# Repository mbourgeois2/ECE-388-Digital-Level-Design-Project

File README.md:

# ECE-388-Digital-Level-Design-Project
This is my Embedded Systems Design Project for ECE-388, the digital level. The design works as follows. The accelerometer will measure the necessary data. The measured data will then be sent to the PINs of the 328PB and the board tilt angle will be calculated. Firmware written on the microcontroller will determine which LEDs in the LED array to light up based on the data given by the accelerometer. This information will then be output from the PORTs of the 328PB and light up the LEDs accordingly. The LEDs will light up in a similar manner to the movement of a bubble in a bubble level. When the board is completely level, the center LED will turn green. 

Demo video: https://youtu.be/xUTPTQpNgwE (could not fit the MP4 file in the repo, had to upload it to youtube)

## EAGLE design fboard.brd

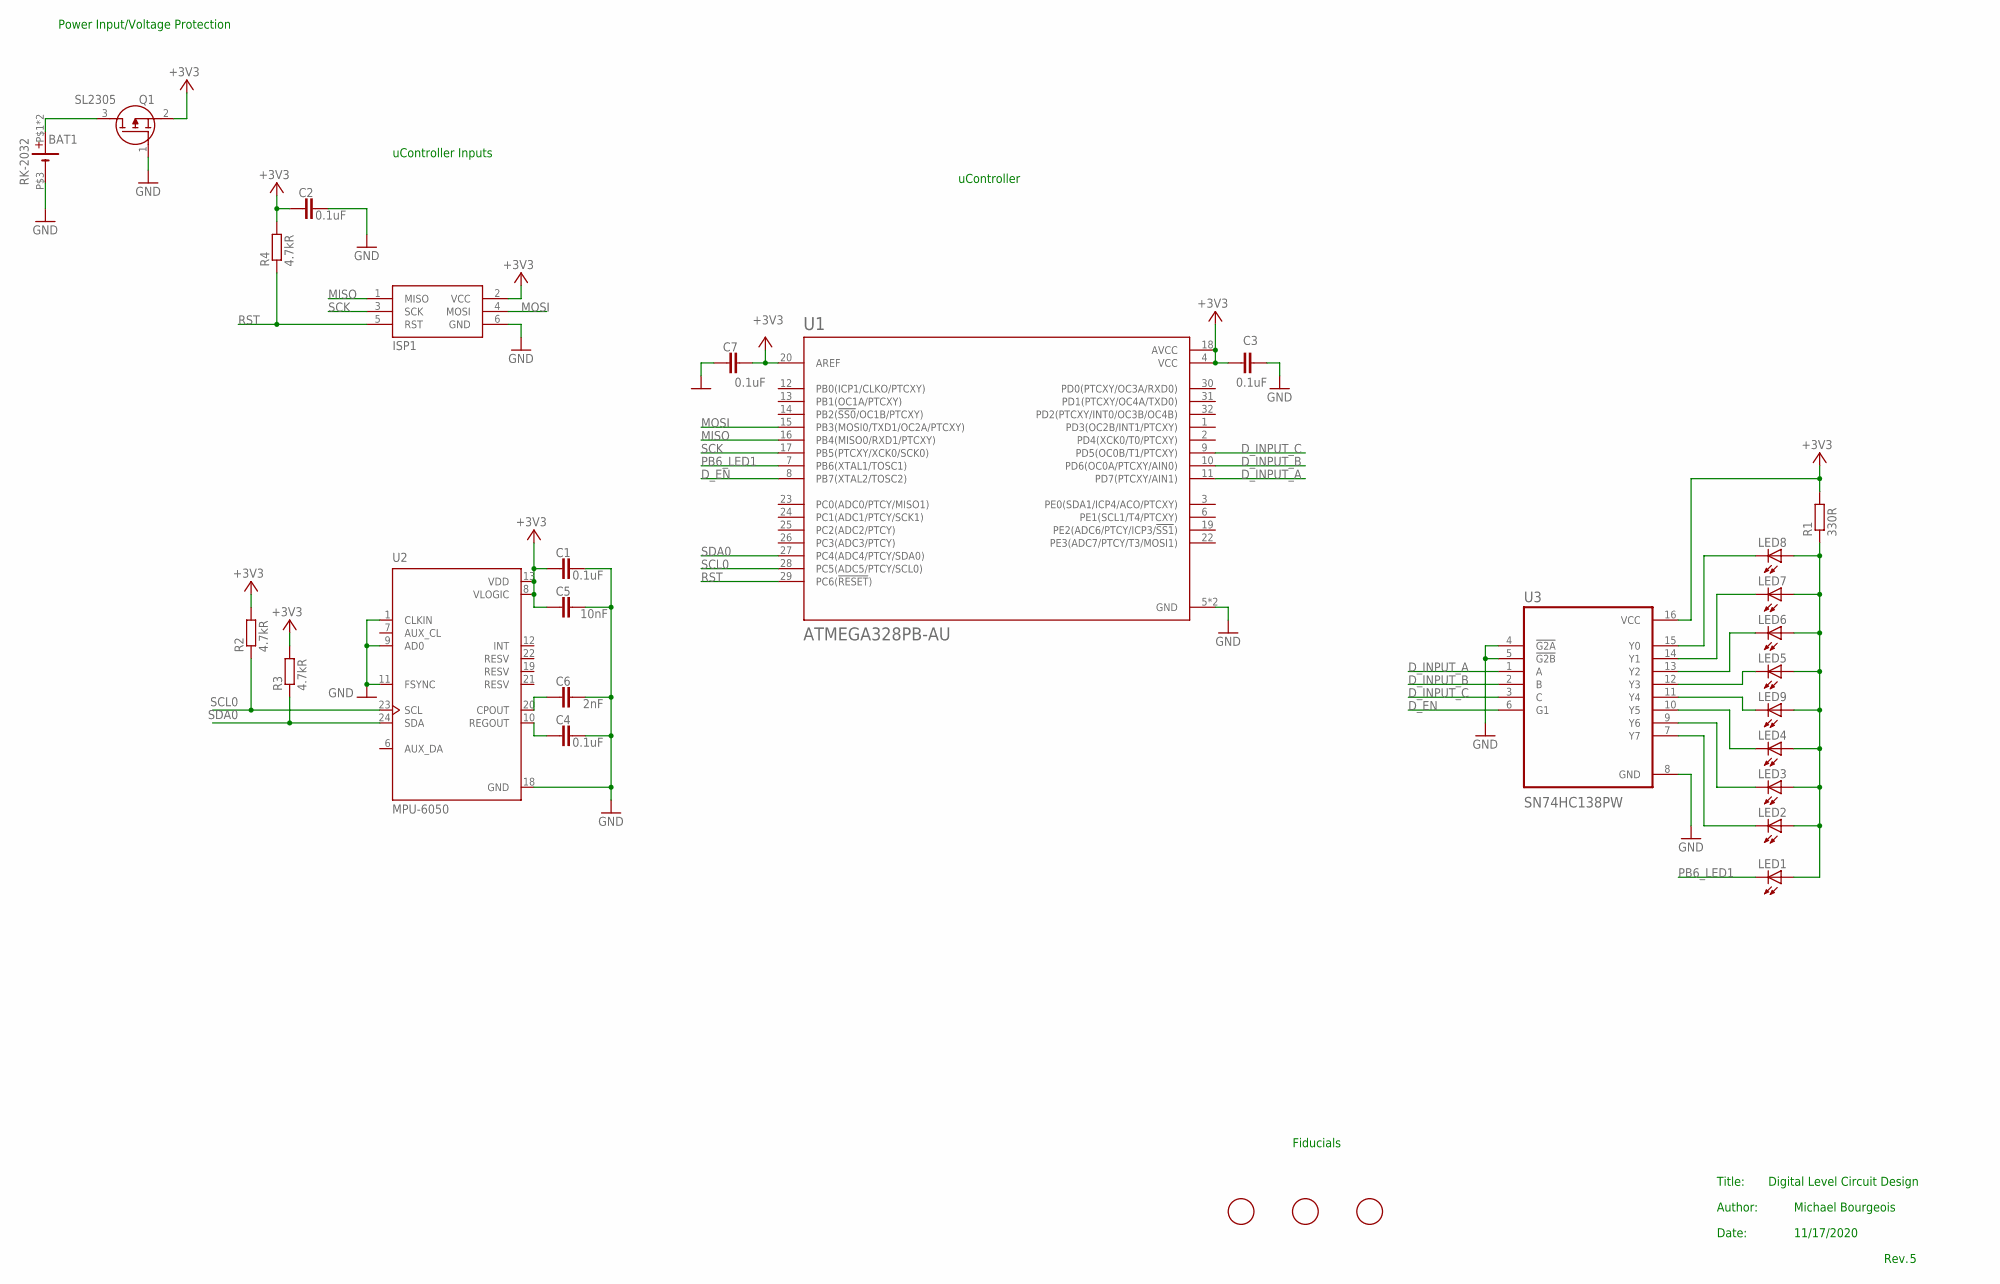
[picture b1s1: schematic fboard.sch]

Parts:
BAT1: RK-2032
C1, C2, C3, C4, C7: 0.1uF; C0805
C5: 10nF; C0805
C6: 2nF; C0805
ISP1: AVRISP-6; AVRISP
LED1, LED2, LED3, LED4, LED5, LED6, LED7, LED8: LEDCHIP-LED0805; CHIP-LED0805
LED9: LEDCHIPLED_0805; CHIPLED_0805
Q1: SL2305; SOT95P240X115-3N
R1: 330R; R0805
R2, R3, R4: 4.7kR; R0805
U1: ATMEGA328PB-AU; QFP80P900X900X120-32N
U2: MPU-6050; QFN50P400X400X95-24N
U3: SN74HC138PW; SOP65P640X120-16N
U$4, U$5, U$6: FIDUCIAL; FIDUCIAL_1MM

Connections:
+3V3: C1.1, C2.1, C3.1, C5.1, C7.1, ISP1.2 (VCC), Q1.2 (S), R1.2, R2.2, R3.2, R4.2, U1.4 (VCC), U1.18 (AVCC), U1.20 (AREF), U2.8 (VLOGIC), U2.13 (VDD), U3.16 (VCC)
D_EN: U1.8 (PB7(XTAL2/TOSC2)), U3.6 (G1)
D_INPUT_A: U1.11 (PD7(PTCXY/AIN1)), U3.1 (A)
D_INPUT_B: U1.10 (PD6(OC0A/PTCXY/AIN0)), U3.2 (B)
D_INPUT_C: U1.9 (PD5(OC0B/T1/PTCXY)), U3.3 (C)
GND: BAT1.P$3 (-), C1.2, C2.2, C3.2, C4.2, C5.2, C6.2, C7.2, ISP1.6 (GND), Q1.1 (G), U1.5 (GND), U1.21 (GND), U2.1 (CLKIN), U2.9 (AD0), U2.11 (FSYNC), U2.18 (GND), U3.4 (!G2A), U3.5 (!G2B), U3.8 (GND)
LED_LINE: LED1.A, LED2.A, LED3.A, LED4.A, LED5.A, LED6.A, LED7.A, LED8.A, LED9.A, R1.1
MISO: ISP1.1 (MISO), U1.16 (PB4(MISO0/RXD1/PTCXY))
MOSI: ISP1.4 (MOSI), U1.15 (PB3(MOSI0/TXD1/OC2A/PTCXY))
unnamed: C4.1, U2.10 (REGOUT)
unnamed: C6.1, U2.20 (CPOUT)
unnamed: BAT1.P$1 (+), BAT1.P$2 (+), Q1.3 (D)
PB6_LED1: LED1.C, U1.7 (PB6(XTAL1/TOSC1))
RST: ISP1.5 (RST), R4.1, U1.29 (PC6(!RESET!))
SCK: ISP1.3 (SCK), U1.17 (PB5(PTCXY/XCK0/SCK0))
SCL0: R2.1, U1.28 (PC5(ADC5/PTCY/SCL0)), U2.23 (SCL)
SDA0: R3.1, U1.27 (PC4(ADC4/PTCY/SDA0)), U2.24 (SDA)
Y0: LED8.C, U3.15 (Y0)
Y1: LED7.C, U3.14 (Y1)
Y2: LED6.C, U3.13 (Y2)
Y3: LED5.C, U3.12 (Y3)
Y4: LED9.C, U3.11 (Y4)
Y5: LED4.C, U3.10 (Y5)
Y6: LED3.C, U3.9 (Y6)
Y7: LED2.C, U3.7 (Y7)

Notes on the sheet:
11/17/2020
Michael Bourgeois
Title:
Digital Level Circuit Design
Author:
Date:
Rev.
Power Input/Voltage Protection
uController Inputs
uController
Fiducials

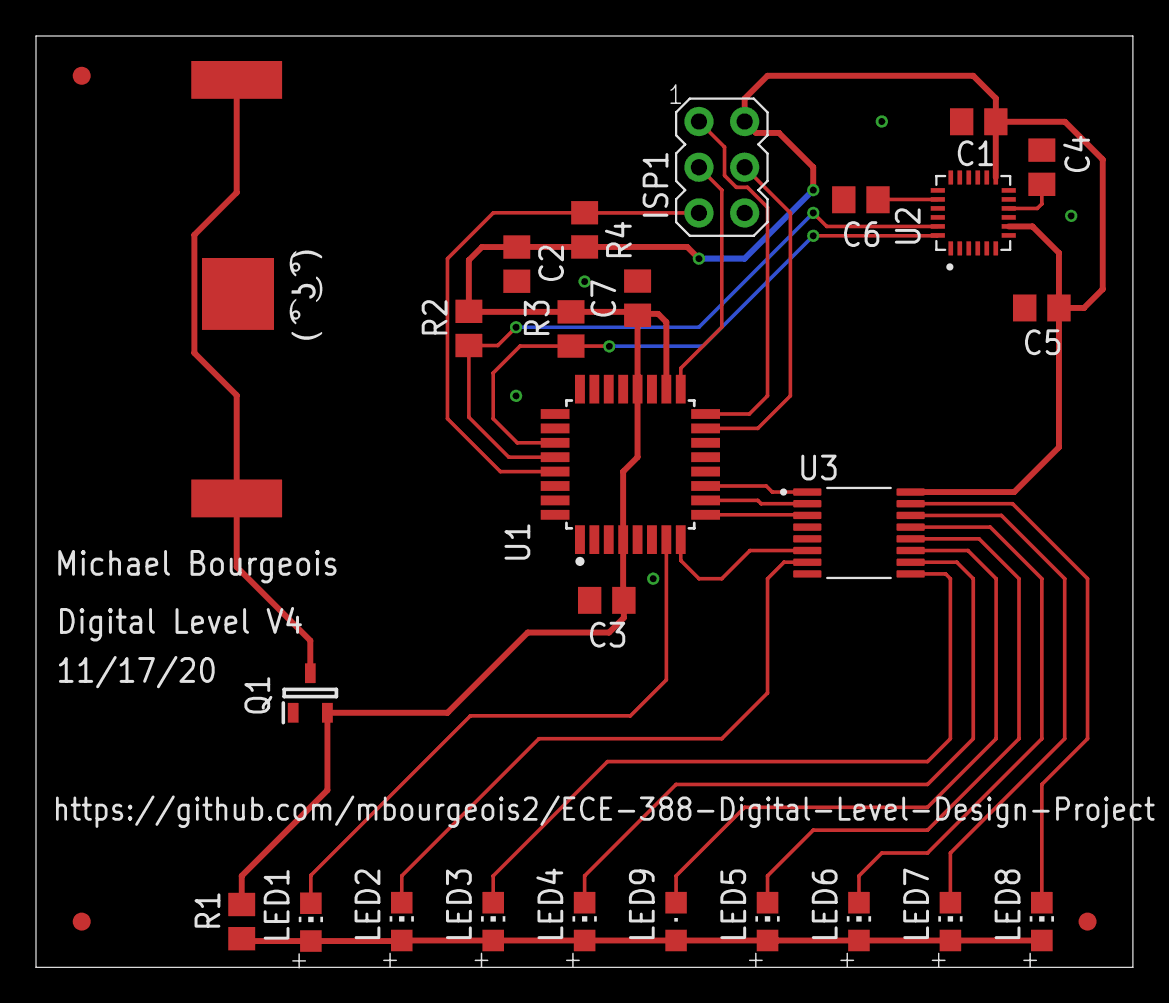
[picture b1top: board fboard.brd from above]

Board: 2 copper layers, 60.9 x 51.7 mm, 29 parts (0 on the bottom side), 25 nets.

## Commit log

2020-10-13 Create cam
2020-11-06 fixed bom
2020-11-06 fixed bom again
2020-11-09 fixed schematic
2020-11-09 fixed more stuff
2020-11-09 edited schematic again
2020-11-09 removed switch
2020-11-09 removed switch from bom
2020-11-09 removed diode and fixed pmos
2020-11-10 fixed schem
2020-11-11 updated stuff
2020-11-11 oops deleted renders folder
2020-11-11 moar schematic
2020-11-11 one tiny little net i had to delete
2020-11-11 board stuff
2020-11-11 moved a capacitor to reduce noise for pullups
2020-11-11 more stuff
2020-11-11 fixed component labels
2020-11-11 fixed labels
2020-11-11 labels
2020-11-11 thicc power traces
2020-11-11 tried to organize silkscreen, also power trace is 13mil
2020-11-12 added easter egg
2020-11-12 bigger font and power traces are 12mil
2020-11-12 ground plane?
2020-11-12 text size and new cam file
2020-11-12 fixed airwire
2020-11-12 redid ground plane
2020-11-12 i know tim checked me off but i noticed q1 was still on the pad
2020-11-12 last minute fixes
2020-11-15 updated bom
2020-11-17 grounded ~g2a and ~g2b
2020-11-17 forgot to increment board version
2020-11-19 added prototype firmware
2020-11-19 added assembly bom
2020-12-03 final code (maybe?)
2020-12-03 fixed some code
